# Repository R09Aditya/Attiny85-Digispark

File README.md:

# Attiny85-Digispark
I am made a digispark attiny85 usb pcb. As this is my first time making a pcb i started with a begginer project and learning through youtube video on step by step guide on making a pcb. It is a very common digispark usb tool used for alot of cybersecurity activities and works quite simmilar like usb rubber ducky.

# Why I made this
First things first, i made this because i just wanted to learn the basic of pcb designing as this is my first time designing a pcb. Also as i am interested into cyber security and ethical hacking i choosed this as my first project.

# Screenshots
## Schematics Image

## PCB Image

## PCB 3d Screenshot Image

## PCB 3d Rendered Image

## Bill of Materials (BOM)

| Reference  | Qty | Value           | Footprint                                                   | Product (link) | Unit price (₹) | Line total (₹) |
|-------------|-----|----------------|-------------------------------------------------------------|----------------|----------------|----------------|
| C1          | 1   | 100n           | Capacitor_SMD:C_1206_3216Metric                             | [1206B104J500NT-FH](https://robu.in/product/1206b104j500nt-fh-50v-100nf-x7r±5-1206-multilayer-ceramic-capacitors-mlcc-smd-smt-rohs) | 3.00  | 3.00  |
| D1, D2      | 2   | 3v6            | Diode_SMD:D_SOD-123                                         | [MM3Z3V6T1G](https://robu.in/product/mm3z3v6t1g-onsemi-independent-3-4v3-8v-300mw-3-6v-sod-323-zener-diodes-rohs) | 7.00  | 14.00 |
| D3          | 1   | LED            | LED_THT:LED_D3.0mm                                          | [5mm Green DIP LED](https://robu.in/product/5mm-green-dip-led-pack-of-50) | 1.66  | 1.66  |
| J1, J2      | 2   | Conn_01x04     | Connector_PinHeader_2.54mm:PinHeader_1x04_P2.54mm_Vertical  | PinHeader_1x04_P2.54mm_Vertical (Robu) | — | — |
| R1, R2      | 2   | 68R            | Resistor_SMD:R_0805_2012Metric_Pad1.20x1.40mm_HandSolder    | [AC0805FR-0768RL-YAGEO](https://robu.in/product/ac0805fr-0768rl-yageo-res-thick-film-0805-68-ohm-1-0-125w1-8w-±100ppm-c-pad-smd-t-r-automotive-aec-q200) | 0.51 | 1.02 |
| R3          | 1   | 330R           | Resistor_SMD:R_0805_2012Metric_Pad1.20x1.40mm_HandSolder    | [RC0805FR-07330RL-YAGEO](https://robu.in/product/rc0805fr-07330rl-yageo-res-thick-film-0805-330-ohm-1-0-125w1-8w-±100ppm-c-pad-smd-t-r) | 0.25 | 0.25 |
| R4          | 1   | 1k5            | Resistor_SMD:R_0805_2012Metric_Pad1.20x1.40mm_HandSolder    | [RC0805FR-071K5L-YAGEO](https://robu.in/product/rc0805fr-071k5l-yageo-res-thick-film-0805-1-5k-ohm-1-0-125w1-8w-±100ppm-c-pad-smd-t-r) | 0.25 | 0.25 |
| U1          | 1   | ATtiny85-20S   | Package_SO:SOIC-8_5.3x5.3mm_P1.27mm                         | [ATTINY85-20SUR](https://robu.in/product/attiny85-20sur-microchip-8-bit-mcu-avr-attiny-family-attiny85-series-microcontrollers-avr-20-mhz-8-kb-8-pins-soij) | 262.00 | 262.00 |
| U2          | 1   | ~              | My_cust_footprint:Untitled                                  | Custom / TBD (Robu) | — | — |
| PCB         | 1   | 2-layer PCB    | Custom PCB (Digispark ATTiny85 USB)                         | PCB Printing Service (Robu) | 5163.00 | 5163.00 |

---

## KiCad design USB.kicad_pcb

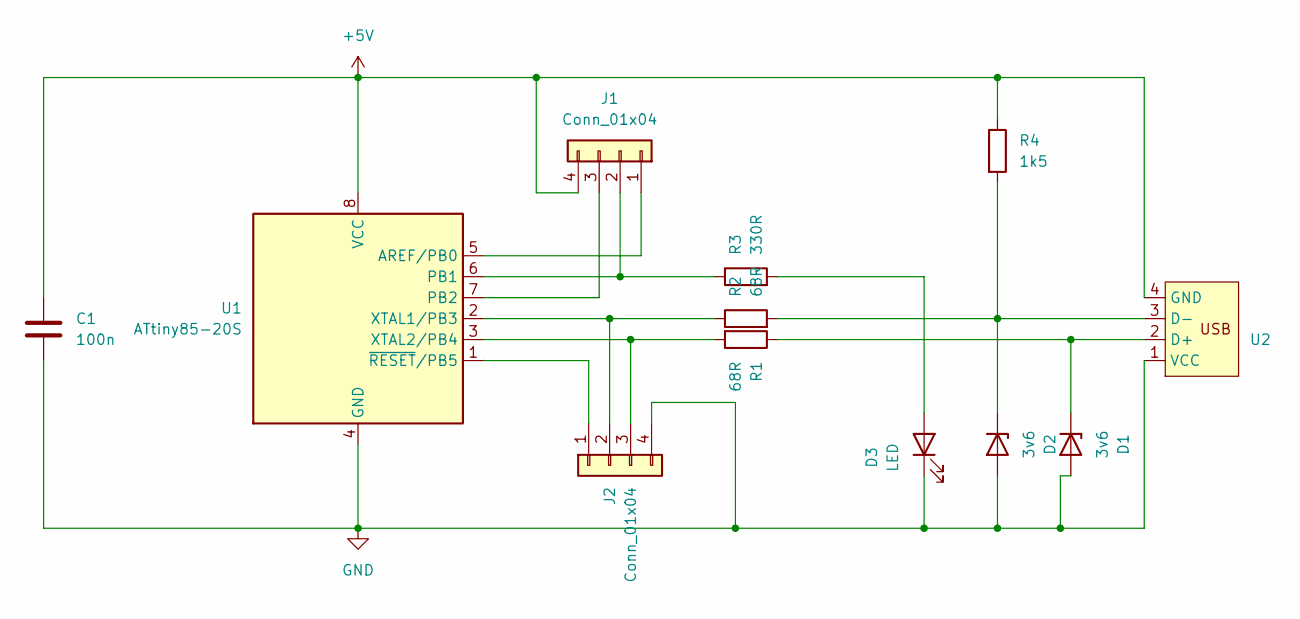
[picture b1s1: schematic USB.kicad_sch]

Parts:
C1: 100n; C_1206_3216Metric
D1, D2: 3v6; D_SOD-123
D3: LED; LED_D3.0mm
J1, J2: Conn_01x04; PinHeader_1x04_P2.54mm_Vertical
R1, R2: 68R; R_0805_2012Metric_Pad1.20x1.40mm_HandSolder
R3: 330R; R_0805_2012Metric_Pad1.20x1.40mm_HandSolder
R4: 1k5; R_0805_2012Metric_Pad1.20x1.40mm_HandSolder
U1: ATtiny85-20S; SOIC-8_5.3x5.3mm_P1.27mm
U2: Untitled

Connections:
+5V: C1.1, J1.4, R4.1, U1.8 (VCC), U2.4 (GND)
GND: C1.2, D1.2 (A), D2.2 (A), D3.1 (K), J2.4, U1.4 (GND), U2.1 (VCC)
unnamed: D1.1 (K), R1.1, U2.2 (D+)
unnamed: D2.1 (K), R2.2, R4.2, U2.3 (D-)
unnamed: D3.2 (A), R3.2
unnamed: J1.1, U1.5 (AREF/PB0)
unnamed: J1.2, R3.1, U1.6 (PB1)
unnamed: J1.3, U1.7 (PB2)
unnamed: J2.1, U1.1 (~RESET/PB5)
unnamed: J2.2, R2.1, U1.2 (XTAL1/PB3)
unnamed: J2.3, R1.2, U1.3 (XTAL2/PB4)

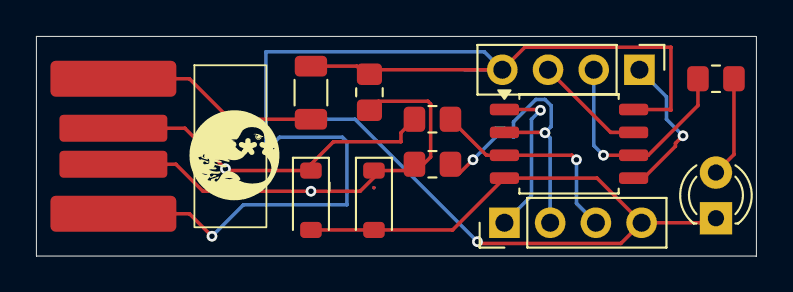
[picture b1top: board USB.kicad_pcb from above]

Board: 2 copper layers, 40.0 x 12.2 mm, 12 parts (0 on the bottom side), 11 nets.

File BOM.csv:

Reference,Qty,Value,Footprint,Product (link),Unit price (₹),Line total (₹)
C1,1,100n,Capacitor_SMD:C_1206_3216Metric,https://robu.in/product/1206b104j500nt-fh-50v-100nf-x7r±5-12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,3,3
"D1, D2",2,3v6,Diode_SMD:D_SOD-123,https://robu.in/product/mm3z3v6t1g-onsemi-independent-3-4v3-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,7,14
D3,1,LED,LED_THT:LED_D3.0mm,https://robu.in/product/5mm-green-dip-led-pack-of-50,1.66,1.66
"J1, J2",2,Conn_01x04,Connector_PinHeader_2.54mm:PinHeader_1x04_P2.54mm_Vertical,PinHeader_1x04_P2.54mm_Vertical (Robu),,
"R1, R2",2,68R,Resistor_SMD:R_0805_2012Metric_Pad1.20x1.40mm_HandSolder,https://robu.in/product/ac0805fr-0768rl-yageo-res-thick-film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,0.51,1.02
R3,1,330R,Resistor_SMD:R_0805_2012Metric_Pad1.20x1.40mm_HandSolder,https://robu.in/product/rc0805fr-07330rl-yageo-res-thick-fil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,0.25,0.25
R4,1,1k5,Resistor_SMD:R_0805_2012Metric_Pad1.20x1.40mm_HandSolder,https://robu.in/product/rc0805fr-071k5l-yageo-res-thick-film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,0.25,0.25
U1,1,ATtiny85-20S,Package_SO:SOIC-8_5.3x5.3mm_P1.27mm,https://robu.in/product/attiny85-20sur-microchip-8-bit-mcu-a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,262,262
U2,1,~,My_cust_footprint:Untitled,Custom / TBD (Robu),,
PCB,1,2-layer PCB,Custom PCB (Digispark ATTiny85 USB),PCB Printing Service (Robu),5163,5163

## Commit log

2025-11-06 Rename Screenshot 2025-11-05 234610.png to schematic.png
2025-11-06 Rename Screenshot 2025-11-06 172251.png to PCB_3d_screenshot.png
2025-11-06 Rename Screenshot 2025-11-06 155556.png to PCB.png
2025-11-06 Rename digispark_attiny_85_1.png to PCB_3d_render.png
2025-11-06 Fix formatting in README.md
    Corrected formatting and spacing in README sections.
2025-11-08 Fix formatting for Bill of Materials section
2025-11-10 Update PCB cost in README
2025-11-10 Remove M1 and B1 components from README
    Removed M1 and B1 components from the parts list.
